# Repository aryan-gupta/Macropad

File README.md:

# Macropad
A test macropad I created to learn KiCAD and how mechanical keyboards work

More info at [my blog](http://theguptaempire.net/dusk-keyboard-part-2/)

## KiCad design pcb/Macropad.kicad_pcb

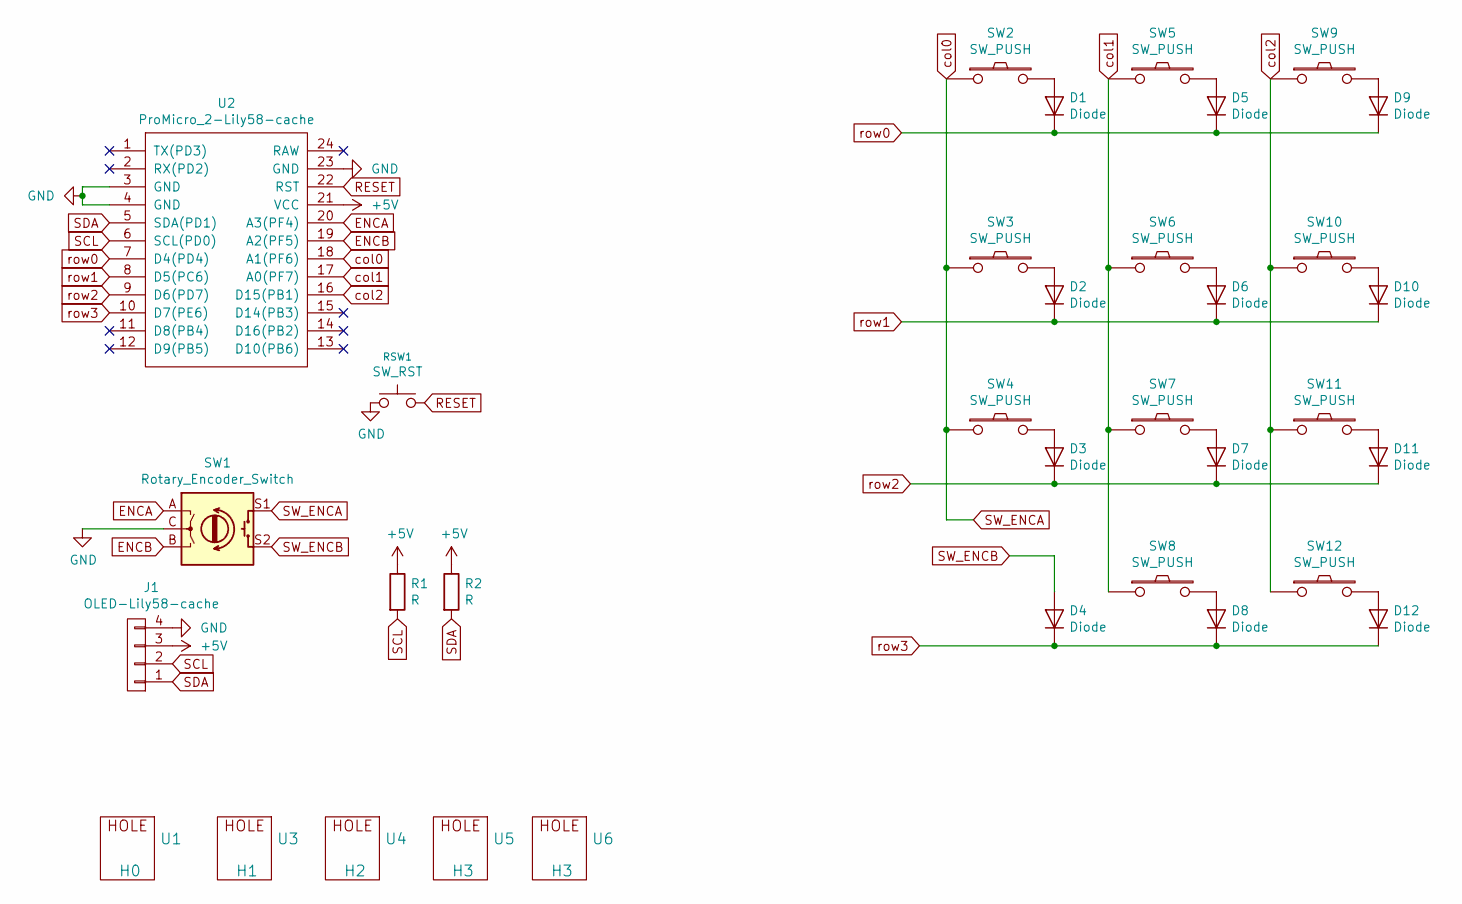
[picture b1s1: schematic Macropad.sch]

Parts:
D1, D2, D3, D4, D5, D6, D7, D8, D9, D10, D11, D12: Diode; Diode_SOD123
J1: OLED-Lily58-cache; OLED_4Pin
R1, R2: R; RESISTOR_mini
RSW1: SW_RST; TACT_SWITCH_TVBP06
SW1: Rotary_Encoder_Switch; RotaryEncoder_Alps_EC11E-Switch_Vertical_H20mm-keebio_modif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
SW2, SW3, SW4, SW5, SW6, SW7, SW9, SW10, SW11, SW12: SW_PUSH; CherryMX_KailhLowProfile_Hotswap
SW8: SW_PUSH; CherryMX_KailhLowProfile_Hotswap_1.5
U1: H0; M2_HOLE_PCB
U2: ProMicro_2-Lily58-cache; ProMicro
U3: H1; M2_HOLE_PCB
U4: H2; M2_HOLE_PCB
U5, U6: H3; M2_HOLE_PCB

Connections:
+5V: J1.3, R1.1, R2.1, U2.21 (VCC)
ENCA: SW1.A, U2.20 (A3(PF4))
ENCB: SW1.B, U2.19 (A2(PF5))
GND: J1.4, RSW1.1, SW1.C, U2.3 (GND), U2.4 (GND), U2.23 (GND)
unnamed: D1.2 (A), SW2.2
unnamed: D2.2 (A), SW3.2
unnamed: D3.2 (A), SW4.2
unnamed: D5.2 (A), SW5.2
unnamed: D6.2 (A), SW6.2
unnamed: D7.2 (A), SW7.2
unnamed: D8.2 (A), SW8.2
unnamed: D9.2 (A), SW9.2
unnamed: D10.2 (A), SW10.2
unnamed: D11.2 (A), SW11.2
unnamed: D12.2 (A), SW12.2
RESET: RSW1.2, U2.22 (RST)
SCL: J1.2, R1.2, U2.6 (SCL(PD0))
SDA: J1.1, R2.2, U2.5 (SDA(PD1))
SW_ENCA: SW1.S1, SW2.1, SW3.1, SW4.1, U2.18 (A1(PF6))
SW_ENCB: D4.2 (A), SW1.S2
col1: SW5.1, SW6.1, SW7.1, SW8.1, U2.17 (A0(PF7))
col2: SW9.1, SW10.1, SW11.1, SW12.1, U2.16 (D15(PB1))
row0: D1.1 (K), D5.1 (K), D9.1 (K), U2.7 (D4(PD4))
row1: D2.1 (K), D6.1 (K), D10.1 (K), U2.8 (D5(PC6))
row2: D3.1 (K), D7.1 (K), D11.1 (K), U2.9 (D6(PD7))
row3: D4.1 (K), D8.1 (K), D12.1 (K), U2.10 (D7(PE6))

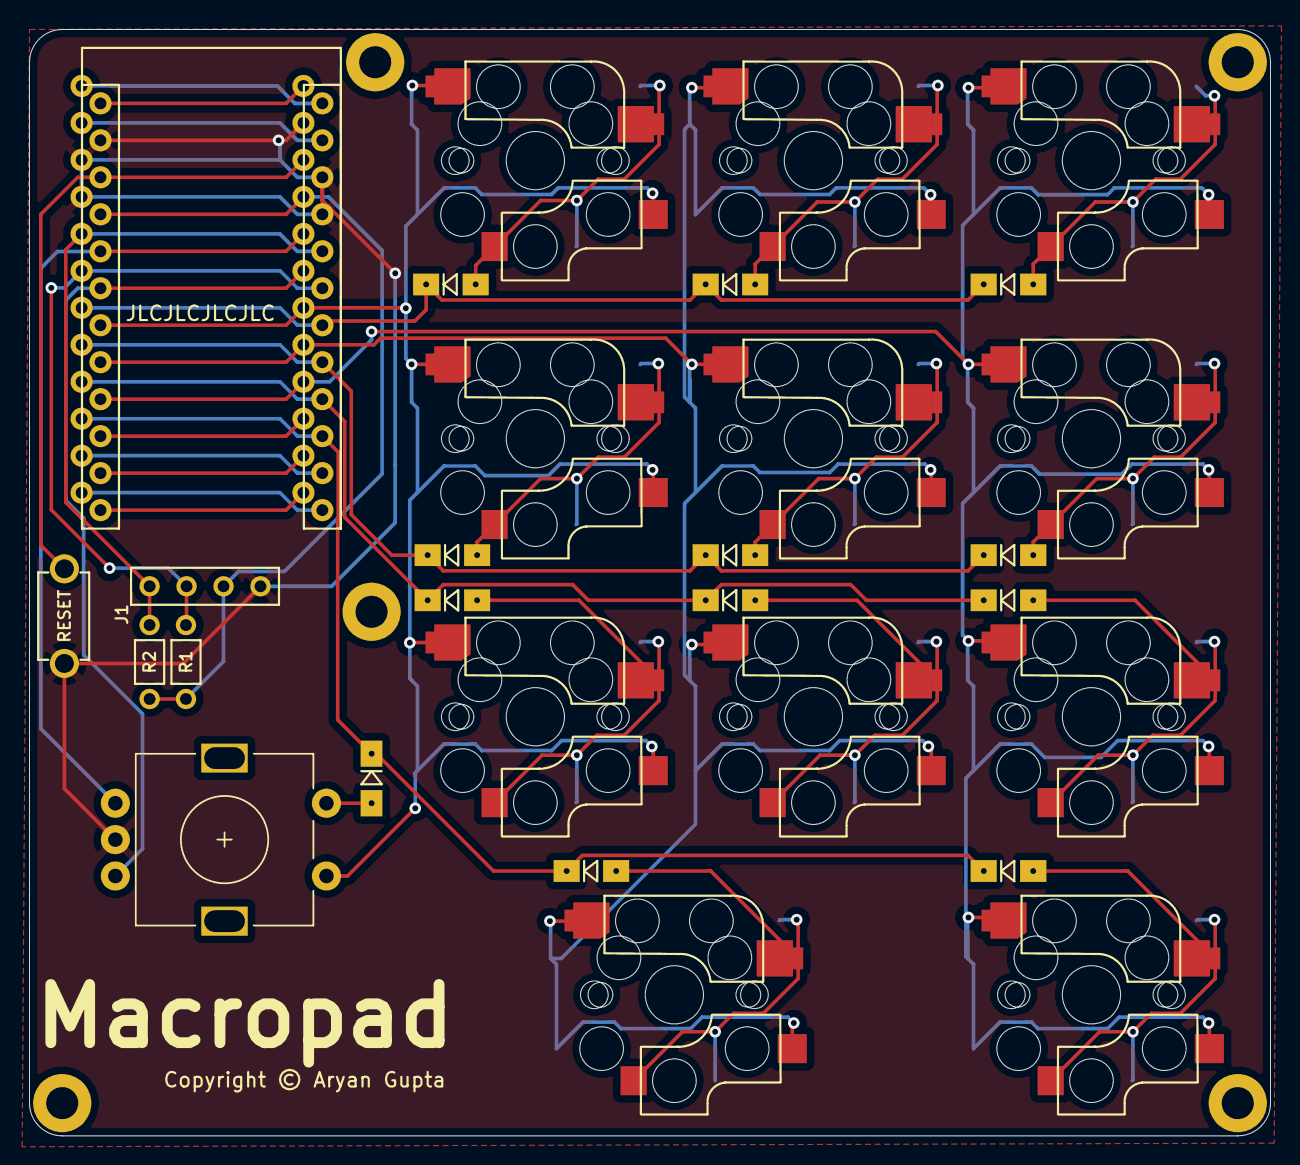
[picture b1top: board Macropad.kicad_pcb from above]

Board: 2 copper layers, 85.2 x 76.0 mm, 34 parts (0 on the bottom side), 26 nets.

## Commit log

2020-11-09 Initial add files
2020-11-09 Add README.md
2020-11-09 Add pdf schematic

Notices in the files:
pcb/Macropad.kicad_pcb:
Copyright © Aryan Gupta
